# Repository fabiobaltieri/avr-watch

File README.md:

AVR Watch
=========

This project is small wrist watch using an AVR microcontroller, a 7-segment
display and the V-USB soft-usb stack.

License
-------

This program is free software: you can redistribute it and/or modify
it under the terms of the GNU General Public License as published by
the Free Software Foundation, either version 2 of the License, or
(at your option) any later version.

Contents
--------

    COPYING     text version of the GPL
    README      this file
    bootloader/ source directory for bootloader
    firmware/   source directory for firmware
    hardware/   source directory for the hardware design
    scripts/    support scripts

Bootloader
----------

Building the bootloader requires an avr-gcc toolchain, in the bootloader/
directory, to build run:

    make

Flashing the firmware on the device requires avrdude and a compatible hardware
programmer. Default configuration is stored at the beginning of the Makefile.
To program with the default configuration, run:

    make load

Fuses can be programmed running:

    make fuse

Firmware
--------

Building the firmwware requires an avr-gcc toolchain, in the firmware/
directory, to build run:

    make

Flashing the firmware on the device requires avrdude and a compatible hardware
programmer. Default configuration is stored at the beginning of the Makefile.
To program with the default configuration, run:

    make load

or using the bootloader (this will reset the device if possible):

    make boot

Hardware
--------

All hardware files (schematic, layout and libraries) are in CadSoft Eagle
format.

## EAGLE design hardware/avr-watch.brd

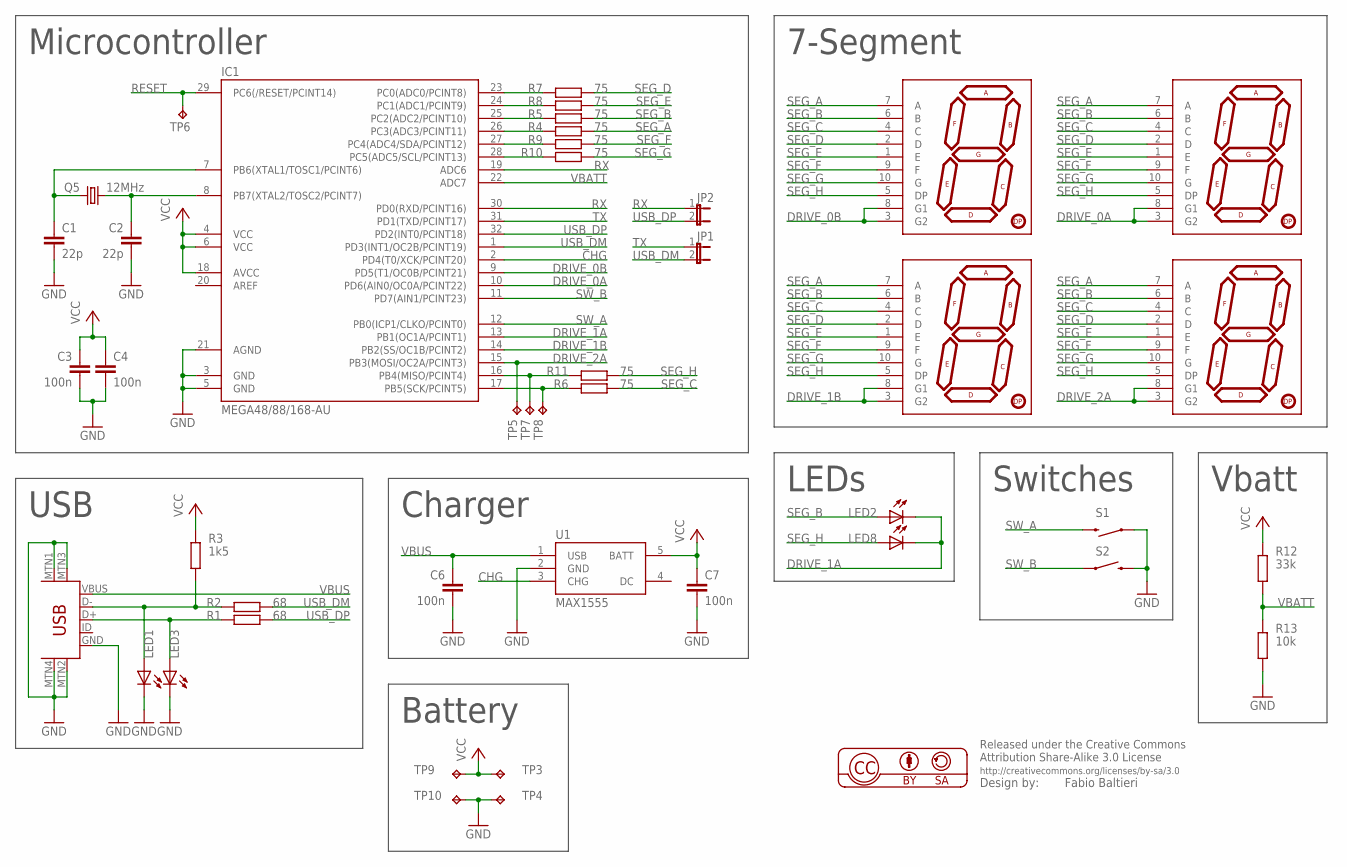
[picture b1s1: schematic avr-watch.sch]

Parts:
C1, C2: 22p; C0805
C3, C4, C6, C7: 100n; C0805
IC1: MEGA48/88/168-AU; TQFP32-08
JP1, JP2: JUMPER-2SMD-NC; SJ_2S
LED1, LED2, LED3, LED8: LEDCHIPLED_1206; CHIPLED_1206
Q5: 12MHz; CTS406
R1, R2: 68; R0603
R3: 1k5; R0603
R4, R5, R6, R7, R8, R9, R10, R11: 75; R0603
R12: 33k; R0603
R13: 10k; R0603
S1, S2: SWITCH-MOMENTARY-2SMD; TACTILE_SWITCH_SMD
TP3, TP4: TPB1,27; B1,27
TP5, TP6, TP7, TP8, TP9, TP10: TPTP08R; TP08R
U1: MAX1555; SOT23-5
U$1, U$3, U$4, U$5: 7-SEGMENT-DISPLAY-1"-RED; 7-SEGMENT-SMD
U$2: USB-MINIB-5PIN; USB-MINIB

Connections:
CHG: IC1.2 (PD4(T0/XCK/PCINT20)), U1.3 (CHG)
DRIVE_0A: IC1.10 (PD6(AIN0/OC0A/PCINT22)), U$3.3 (G2), U$3.8 (G1)
DRIVE_0B: IC1.9 (PD5(T1/OC0B/PCINT21)), U$1.3 (G2), U$1.8 (G1)
DRIVE_1A: IC1.13 (PB1(OC1A/PCINT1)), LED2.C, LED8.C
DRIVE_1B: IC1.14 (PB2(SS/OC1B/PCINT2)), U$4.3 (G2), U$4.8 (G1)
DRIVE_2A: IC1.15 (PB3(MOSI/OC2A/PCINT3)), TP5.TP, U$5.3 (G2), U$5.8 (G1)
GND: C1.2, C2.2, C3.2, C4.2, C6.2, C7.2, IC1.3 (GND), IC1.5 (GND), IC1.21 (AGND), LED1.C, LED3.C, R13.1, S1.1, S2.3 (2), TP4.TP, TP10.TP, U1.2 (GND), U$2.GND, U$2.MTN1 (MTN2), U$2.MTN2 (MTN3), U$2.MTN3 (MTN1), U$2.MTN4
unnamed: C2.1, IC1.8 (PB7(XTAL2/TOSC2/PCINT7)), Q5.3 (2)
unnamed: C1.1, IC1.7 (PB6(XTAL1/TOSC1/PCINT6)), Q5.1
unnamed: IC1.16 (PB4(MISO/PCINT4)), R11.1, TP7.TP
unnamed: IC1.17 (PB5(SCK/PCINT5)), R6.1, TP8.TP
unnamed: IC1.24 (PC1(ADC1/PCINT9)), R8.1
unnamed: IC1.25 (PC2(ADC2/PCINT10)), R5.1
unnamed: IC1.26 (PC3(ADC3/PCINT11)), R4.1
unnamed: IC1.27 (PC4(ADC4/SDA/PCINT12)), R9.1
unnamed: IC1.23 (PC0(ADC0/PCINT8)), R7.1
unnamed: IC1.28 (PC5(ADC5/SCL/PCINT13)), R10.1
unnamed: LED1.A, R2.1, R3.1, U$2.D-
unnamed: LED3.A, R1.1, U$2.D+
RESET: IC1.29 (PC6(/RESET/PCINT14)), TP6.TP
RX: IC1.19 (ADC6), IC1.30 (PD0(RXD/PCINT16)), JP2.1
SEG_A: R4.2, U$1.7 (A), U$3.7 (A), U$4.7 (A), U$5.7 (A)
SEG_B: LED2.A, R5.2, U$1.6 (B), U$3.6 (B), U$4.6 (B), U$5.6 (B)
SEG_C: R6.2, U$1.4 (C), U$3.4 (C), U$4.4 (C), U$5.4 (C)
SEG_D: R7.2, U$1.2 (D), U$3.2 (D), U$4.2 (D), U$5.2 (D)
SEG_E: R8.2, U$1.1 (E), U$3.1 (E), U$4.1 (E), U$5.1 (E)
SEG_F: R9.2, U$1.9 (F), U$3.9 (F), U$4.9 (F), U$5.9 (F)
SEG_G: R10.2, U$1.10 (G), U$3.10 (G), U$4.10 (G), U$5.10 (G)
SEG_H: LED8.A, R11.2, U$1.5 (DP), U$3.5 (DP), U$4.5 (DP), U$5.5 (DP)
SW_A: IC1.12 (PB0(ICP1/CLKO/PCINT0)), S1.3 (2)
SW_B: IC1.11 (PD7(AIN1/PCINT23)), S2.1
TX: IC1.31 (PD1(TXD/PCINT17)), JP1.1
USB_DM: IC1.1 (PD3(INT1/OC2B/PCINT19)), JP1.2, R2.2
USB_DP: IC1.32 (PD2(INT0/PCINT18)), JP2.2, R1.2
VBATT: IC1.22 (ADC7), R12.1, R13.2
VBUS: C6.1, U1.1 (USB), U$2.VBUS
VCC: C3.1, C4.1, C7.1, IC1.4 (VCC), IC1.6 (VCC), IC1.18 (AVCC), R3.2, R12.2, TP3.TP, TP9.TP, U1.5 (BATT)

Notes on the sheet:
USB
Microcontroller
7-Segment
LEDs
Charger
Switches
Vbatt
Battery

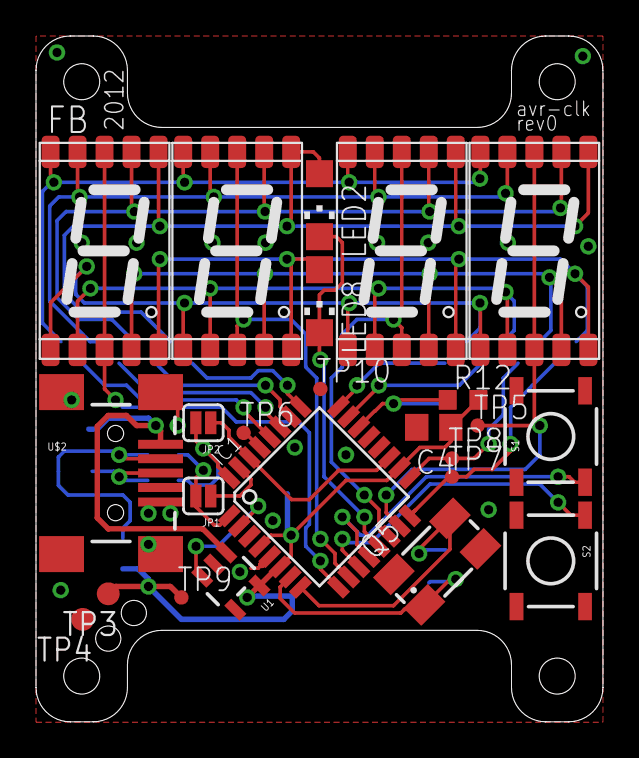
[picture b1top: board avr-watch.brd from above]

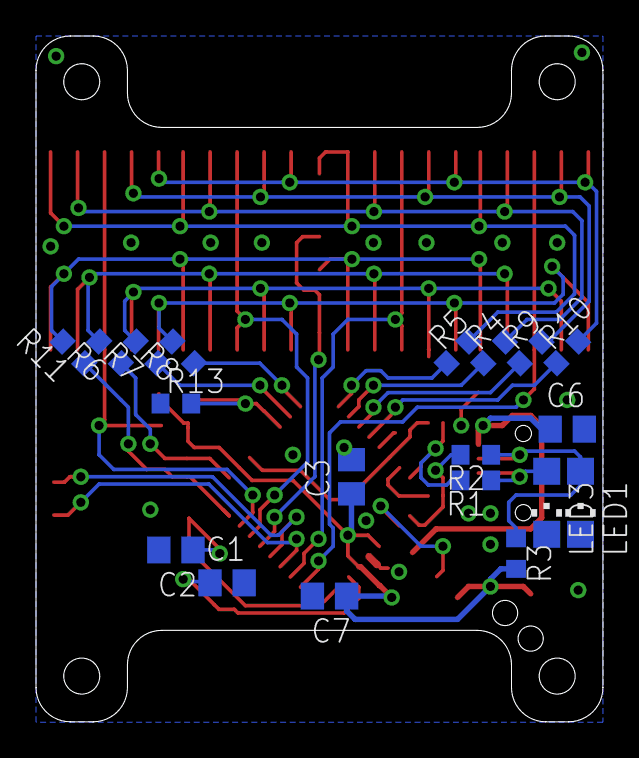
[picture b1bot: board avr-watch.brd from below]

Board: 2 copper layers, 31.5 x 38.1 mm, 43 parts (19 on the bottom side), 37 nets.

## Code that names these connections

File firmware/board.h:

/* LEDs */

#define SSEG_A	PC3
#define SSEG_B	PC2
#define SSEG_D	PC0
#define SSEG_E	PC1
#define SSEG_F	PC4
#define SSEG_G	PC5
#define SSEG_C	PB5
#define SSEG_H	PB4

#define SSEG_PORT_D01	PORTD
#define SSEG_DDR_D01	DDRD
#define SSEG_PORT_D234	PORTB
#define SSEG_DDR_D234	DDRB

#define SSEG_D0	PD5 /* OC0B */
#define SSEG_D1	PD6 /* OC0A */
#define SSEG_D2	PB2 /* OC1B */
#define SSEG_D3	PB3 /* OC2A */
#define SSEG_D4	PB1 /* OC1A */

#define drive_0(x) do {					\
		if (x)					\
			SSEG_DDR_D01 |= _BV(SSEG_D0);	\
		else					\
			SSEG_DDR_D01 &= ~_BV(SSEG_D0);	\
	} while (0)
#define drive_1(x) do {					\
		if (x)					\
			SSEG_DDR_D01 |= _BV(SSEG_D1);	\
		else					\
			SSEG_DDR_D01 &= ~_BV(SSEG_D1);	\
	} while (0)
#define drive_2(x) do {					\
		if (x)					\
			SSEG_DDR_D234  |= _BV(SSEG_D2);	\
		else					\
			SSEG_DDR_D234 &= ~_BV(SSEG_D2);	\
	} while (0)
#define drive_3(x) do {					\
		if (x)					\
			SSEG_DDR_D234  |= _BV(SSEG_D3);	\
		else					\
			SSEG_DDR_D234 &= ~_BV(SSEG_D3);	\
	} while (0)
#define drive_4(x) do {					\
		if (x)					\
			SSEG_DDR_D234  |= _BV(SSEG_D4);	\
		else					\
			SSEG_DDR_D234 &= ~_BV(SSEG_D4);	\
	} while (0)

#define led_init() do {				\
		DDRC |= 0x3f;			\
		DDRB |= 0x30;			\
	} while (0)

#define led_set(x) do {						\
		PORTC = (PORTC & ~0x3f) | (x & 0x3f);		\
		PORTB = (PORTB & ~0x30) | ((x & 0xc0) >> 2);	\
	} while (0)

/* Buttons */

#define SW_A_PCINT	PCINT0
#define SW_A_PCMSK	PCMSK0
#define SW_A_PORT	PORTB
#define SW_A_PIN	PINB
#define SW_A		PB0

#define SW_B_PCINT	PCINT23
#define SW_B_PCMSK	PCMSK2
#define SW_B_PORT	PORTD
#define SW_B_PIN	PIND
#define SW_B		PD7

#define sw_init() do {				\
		SW_A_PORT |= _BV(SW_A);		\
		SW_B_PORT |= _BV(SW_B);		\
		SW_A_PCMSK |= _BV(SW_A_PCINT);	\
		SW_B_PCMSK |= _BV(SW_B_PCINT);	\
	} while (0)

#define sw_a_read() (!(SW_A_PIN & _BV(SW_A)))
#define sw_b_read() (!(SW_B_PIN & _BV(SW_B)))

/* CHG */
#define CHG_PCINT	PCINT20
#define CHG_PCMSK	PCMSK2
#define CHG_PORT	PORTD
#define CHG_PIN		PIND
#define CHG		PD4

#define chg_init() do {				\
		CHG_PORT |= _BV(CHG);		\
		CHG_PCMSK |= _BV(CHG_PCINT);	\
	} while (0)

#define chg_read() (!(CHG_PIN & _BV(CHG)))

/* Analog */

#define AIN_BATTERY	(_BV(REFS0) | 0x0e) /* measure Vbg, AVcc reference */

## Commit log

2011-12-11 hardware: initial hardware files import
2011-12-11 hardware: add silkscreen
2011-12-12 hardware: add rx-adc connection
2012-02-14 firmware: add clean 20120109 usbdrv lib sources
2012-02-14 firmware: add initial Makefile
2012-02-14 firmware: add default usbconfig.h
2012-02-14 bootloader: add original bootloadHID firmware
2012-02-17 bootloader: Makefile: set fuse for ATmega168
2012-02-17 bootloader: setup for ATmega168 on usbasp board
2012-02-17 firmware: add example requests.h
2012-02-17 firmware: clean up of vusb files
2012-02-17 usbconfig: change vendor/product strings
2012-02-17 main: add reset_cpu request
2012-02-23 main: remove typedef to usbRequest
2012-03-26 bootloader: initial port to avr-clock
2012-03-26 firmware: implement clock state machine stubs
2012-03-26 firmware: avr-clock port, add lcd draw logic
2012-03-26 hardware: change led and Vbatt resistors
2012-03-26 firmware: add battery voltage reading function
2012-03-26 firmware: use correct usb data pins
2012-03-26 firmware: add set/get time requests
2012-03-26 firmware: fix clock display
2012-03-26 firmware: blink leds each second
2012-03-26 firmware: usbconfig: change product string
2012-03-26 Makefile: add PRE_BOOTLOADER
2012-03-26 firmware: move real time to timer 1 (16 bits)
2012-03-26 firmware: change step_mark to countdown
2012-03-26 firmware: add usb_toggle function
2012-03-26 firmware: define TICK_COUNT
2012-03-26 firmware: add missing "static" declarations
2012-03-26 firmware: stop screen refresh when not necessary
2012-03-26 firmware: cosmetic fixes
2012-03-26 firmware: rework refresh standby logic
2012-03-26 firmware: add charging indication
2012-03-26 firmware: default usb_enabled 1
2012-03-26 firmware: slow down clock to F_CPU/4 when usb is disabled
2012-03-26 firmware: rise TICK_COUNT to 150
2012-03-27 scripts: add set-time script
2012-03-27 gitignore: add gitignore file
2012-03-28 firmware: disable usb with interrupt mask to save power
2012-04-01 hardware: rename (clock -> watch)
2012-04-01 bootloader: update copyright notice
    Keep GPL2 license, change current author, retain original author
    information.
2012-04-01 firmware: update copyright information
2012-04-01 add readme and license files
2012-04-01 hardware: cosmetic changes, add pdf
2012-05-09 fw: change voltage scaling formula to improve accuracy
2012-06-14 fw: change battery measurement method

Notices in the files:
parts and their libraries:
balto: Released under the Creative Commons
balto: http://creativecommons.org/licenses/by-sa/3.0
